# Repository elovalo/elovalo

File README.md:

<!-- -*- mode: markdown; coding: utf-8 -*- -->

# Elovalo LED Cube Pedestal

You should check out [elovalo.koodilehto.fi](http://elovalo.koodilehto.fi/) for more casual documentation. If you are interested in building the project and developing effects, read on.

## Dependencies

You should have at least gcc, avr-gcc, scons, gperf and preferably
jansson and Blender installed in order to use the simulator. If you
have Ubuntu 12.04 LTS or 12.10, we have instructions for you.

### Ubuntu 14.10

Something went wrong with GCC leading to this project not to compile. We are going to fix this after release of Ubuntu 15.04. If you happen te fix it, please send a patch!

### Ubuntu 12.10

To build on Ubuntu 12.10, install the following packages:

    sudo apt-get install gcc-avr avr-libc gcc scons libjansson-dev gperf avrdude

If you want to generate animations, install the following packages as well:

    sudo apt-get install blender libav-tools

### Ubuntu 12.04

With Ubuntu 12.04 LTS you need to install some packages from Quantal (12.10)
repositories. Here's how to do it:

Add the following lines to <tt>/etc/apt/preferences.d/10-quantal</tt>

    Package: *
    Pin: release a=quantal
    Pin-Priority: 100

And add the following line to <tt>/etc/apt/sources.list</tt>

    deb http://archive.ubuntu.com/ubuntu quantal main restricted universe multiverse

Now you can install all the required packages:

    sudo apt-get install gcc-avr/quantal avr-libc/quantal gcc scons libjansson-dev gperf avrdude

If you want to generate animations, install the following packages as well:

    sudo apt-get install blender libav-tools

The alternative to using quantal-pinning is to fetch the packages from
launchpad. This has only been verified on Kubuntu. You can also skip
the above steps and download the packages straight from the quantal
launchpad:
	
	https://launchpad.net/ubuntu/quantal/amd64/avr-libc/1:1.8.0-2
	https://launchpad.net/ubuntu/quantal/amd64/gcc-avr

If you have a 32bit system (tell 2002 we said *hi*), replace the amd64
from the URL to i386.

### OS X with SCons

Make sure you have at least gcc, avr-gcc and scons
installed. Preferably you should have jansson and Blender (2.6x) as
well if you wish to use the simulator.

In order to render with Blender, you'll need to define an alias
for. Just having it in your path isn't quite enough for some
reason. Add something like this to your .bashrc or .bash\_profile:

    alias blender="path to blender/blender.app/Contents/MacOS/blender"

### Eclipse 

You may use Eclipse for editing but you need SCons because of the complexity of this build (we are using code generation and multiple targets). It may be possible to use SCons in Eclipse if you feel adventurous:
http://stackoverflow.com/questions/1052759/eclipse-cdt-scons

## Building with SCons

The recommended way to build this project is SCons and we have
SCons build file for you. Just run:

    scons

Then the AVR output gets into `build/elo` and `build/zcl` and exporter
stuff to `build/exporter`. To run the exporter:

    build/exporter/exporter

If you want just to play with effets and you don't have an AVR compiler,
you may skip AVR build by running:

    scons --no-avr

## Programming AVR with SCons

If you are running Ubuntu 12.04 or newer and want to be able to flash without
root privileges, add the following udev rule to `/etc/udev/rules.d/10-usbasp`:

    SUBSYSTEM=="usb", ATTR{idVendor}=="16c0", ATTR{idProduct}=="05dc", MODE="0660", GROUP="adm"

Then just reboot your computer (or do some udev magic if you are Linux master).

To program Elocmd variant (the ordinary one), run:

    scons --program-elo
	
To program the variant with Zigbee support, run:

    scons --program-zcl

## Size Optimization

There is enough EEPROM but the SRAM usage is quite high because of
front and back buffers uses 0x300 bytes each. This leaves very scarce
resources for effect development. To see contents of SRAM, run:

    avr-objdump -t -j .data -j .bss build/zcl/release/firmware.elf

Bytes used in SRAM is printed every time scons is run. SRAM size in
ATmega328p is 2048 bytes. If SRAM gets too full, there is not enough
space for run-time stack. If so, you are in need of optimization.

If there are large arrays of constant data you should place the data
in program memory. See code in effects.c and main.c about effects[]
access. Also, read the following:

- http://nongnu.org/avr-libc/user-manual/pgmspace.html

- http://www.atmel.com/Images/doc8453.pdf

## Other

If you study the project further, you'll find more READMEs and more information related to specific parts. Have fun developing effects and whatnot!

## Credits

* [Joni Katajamäki](https://github.com/katis) - Embedded programming, hardware design 
* [Jukka Kinnunen](https://github.com/resutoor) - Hardware design and debugging
* [Joel Lehtonen](https://github.com/Zouppen/) - Embedded programming, effect engine programming
* [Lasse Saari](https://github.com/lassesaari) - Management, pedestal fabrication
* [Marko Silokunnas](https://github.com/marant) - Soldering
* [Mio Taalas](https://github.com/mtaalas/) - LED driver interface design, PCB design,
  embedded programming
* [Ilkka Turunen](https://github.com/ile2/) - Management, soldering, pedestal
  tests and aesthetic design
* [Juho Vepsäläinen](https://github.com/bebraw/) - 3D simulator, effect programming, pedestal
  design

## License

We use GPLv3 for software. Create Commons Attribution-ShareAlike is used for hardware and accompanying documentation. See LICENSE files for more details.

If you create a derivative, please let us know. It would be interesting to hear what you are doing.

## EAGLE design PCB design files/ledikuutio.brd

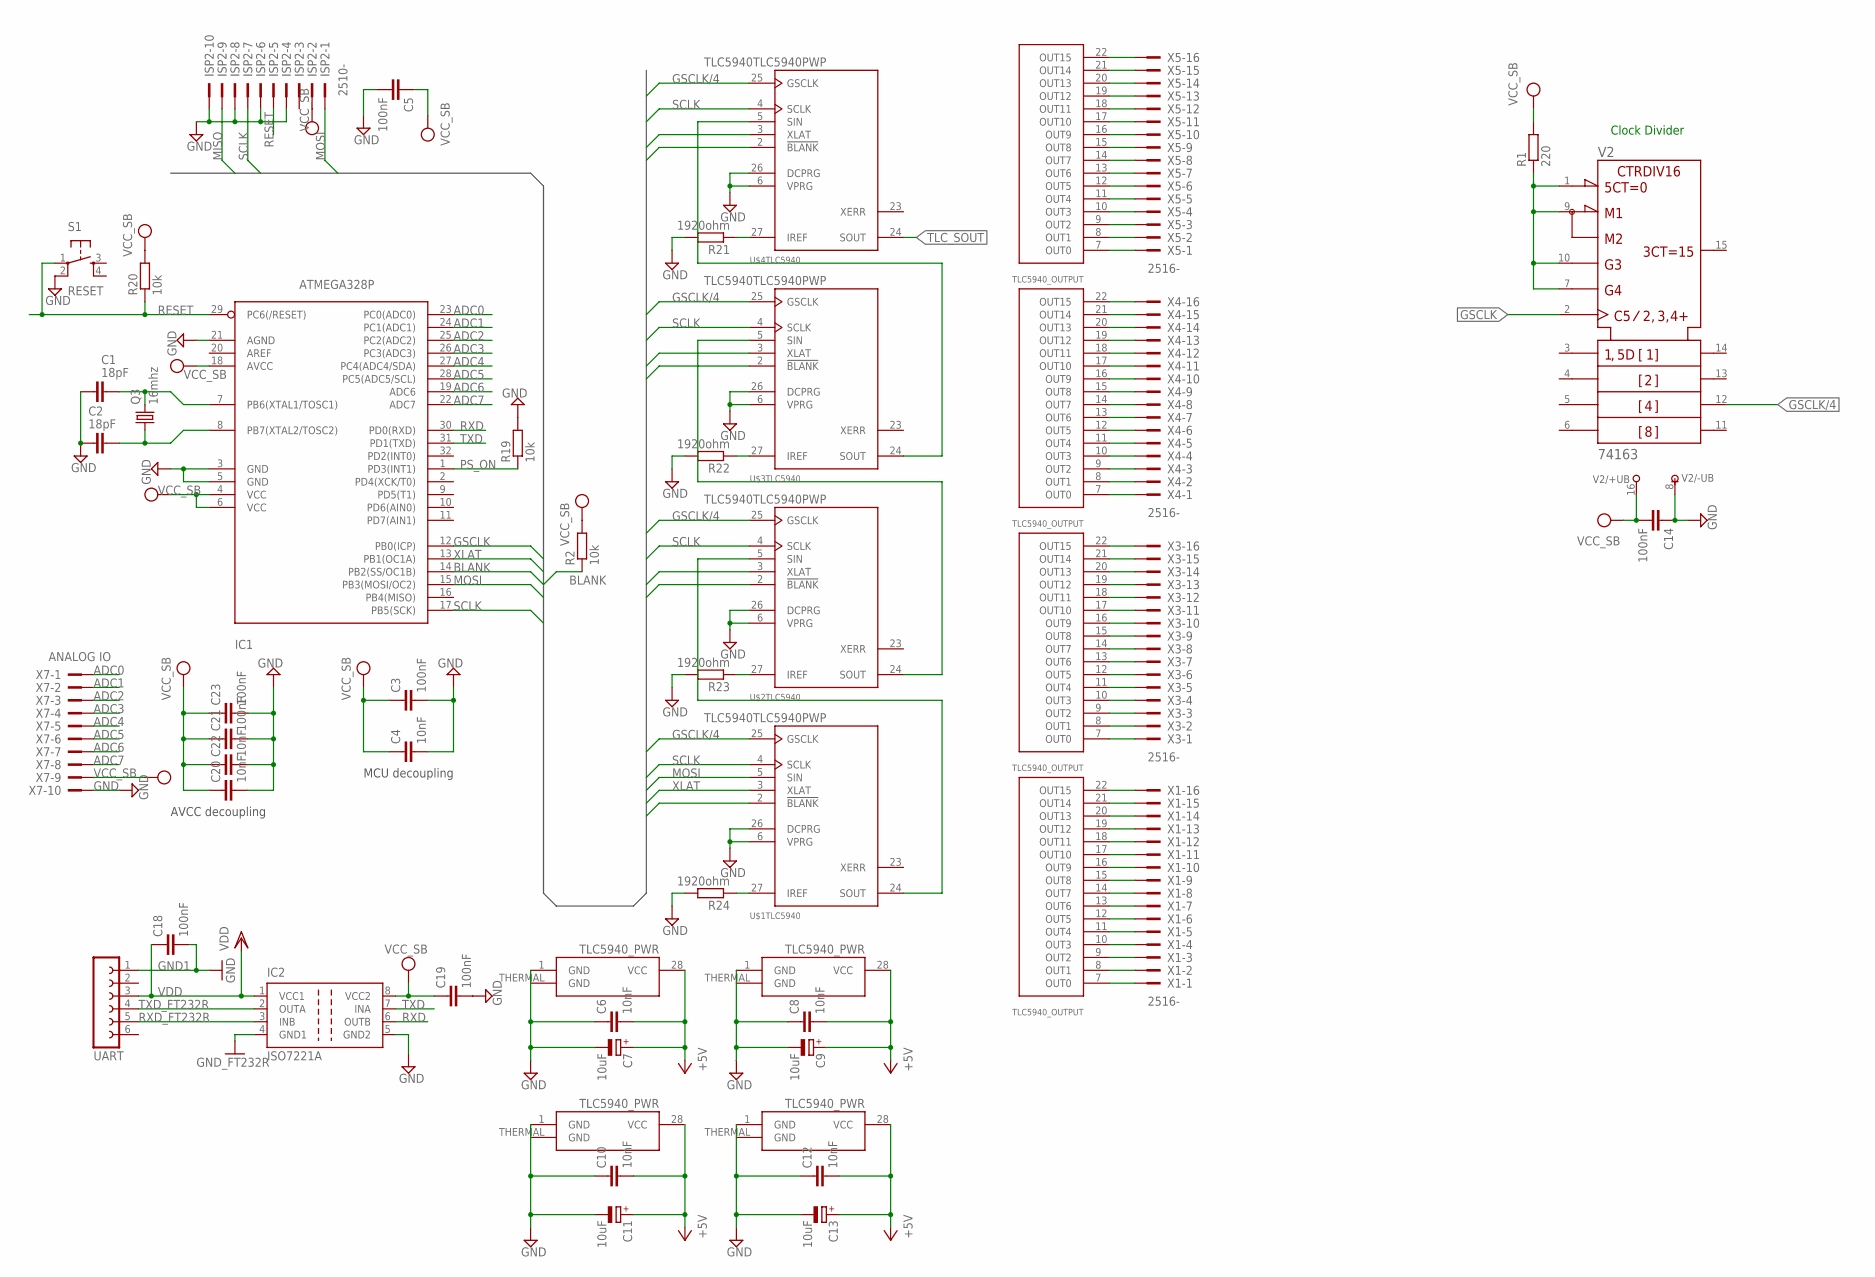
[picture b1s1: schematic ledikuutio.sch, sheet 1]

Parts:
C1, C2: 18pF; C0805
C3, C5, C14, C21, C23: 100nF; C0805
C4, C6, C8, C10, C12, C20, C22: 10nF; C0805
C7, C9, C11, C13: 10uF; E2,5-6
C18, C19: 100nF; C0603
IC1: ATMEGA328P; TQFP32-08
IC2: ISO7221A; SO-08
ISP2: 2510-; PAK100/2500-10
Q3: 16mhz; CRYSTAL-SMD-5X3
R1: 220; M0805
R2, R19, R20: 10k; M0805
R21, R22, R23, R24: 1920ohm; M0805
S1: RESET; TACTILE_SWITCH_SMD
U$1, U$2, U$3, U$4: TLC5940TLC5940PWP; PWP28
UART: FE06-1; FE06
V2: 74163; SO16
X1, X3, X4, X5: 2516-; PAK100/2500-16
X7: ANALOG IO; PAK100/2500-10

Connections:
+5V: C6.2, C7.+, C8.2, C9.+, C10.2, C11.+, C12.2, C13.+, U$1.28 (VCC), U$2.28 (VCC), U$3.28 (VCC), U$4.28 (VCC); also elsewhere on the board
ADC0: IC1.23 (PC0(ADC0)), X7.1
ADC1: IC1.24 (PC1(ADC1)), X7.2
ADC2: IC1.25 (PC2(ADC2)), X7.3
ADC3: IC1.26 (PC3(ADC3)), X7.4
ADC4: IC1.27 (PC4(ADC4/SDA)), X7.5
ADC5: IC1.28 (PC5(ADC5/SCL)), X7.6
ADC6: IC1.19 (ADC6), X7.7
ADC7: IC1.22 (ADC7), X7.8
BLANK: IC1.14 (PB2(SS/OC1B)), R2.1, U$1.2 (!BLANK), U$2.2 (!BLANK), U$3.2 (!BLANK), U$4.2 (!BLANK)
GND: C1.1, C2.2, C3.2, C4.2, C5.2, C6.1, C7.-, C8.1, C9.-, C10.1, C11.-, C12.1, C13.-, C14.1, C19.2, C20.2, C21.2, C22.2, C23.2, IC1.3 (GND), IC1.5 (GND), IC1.21 (AGND), IC2.5 (GND2), ISP2.4, ISP2.6, ISP2.8, ISP2.10, R19.2, R21.2, R22.2, R23.2, R24.2, S1.2, U$1.1 (GND), U$1.6 (VPRG), U$1.26 (DCPRG), U$1.THERMAL (GND), U$2.1 (GND), U$2.6 (VPRG), U$2.26 (DCPRG), U$2.THERMAL (GND), U$3.1 (GND), U$3.6 (VPRG), U$3.26 (DCPRG), U$3.THERMAL (GND), U$4.1 (GND), U$4.6 (VPRG), U$4.26 (DCPRG), U$4.THERMAL (GND), V2.8 (-UB), X7.10; also elsewhere on the board
GND1: C18.2, IC2.4 (GND1), UART.1
GSCLK: IC1.12 (PB0(ICP)), V2.2 (CLK)
GSCLK/4: U$1.25 (GSCLK), U$2.25 (GSCLK), U$3.25 (GSCLK), U$4.25 (GSCLK), V2.12 (QC)
MISO: IC1.16 (PB4(MISO)), ISP2.9
MOSI: IC1.15 (PB3(MOSI/OC2)), ISP2.1, U$1.5 (SIN)
unnamed: U$1.24 (SOUT), U$2.5 (SIN)
unnamed: C1.2, IC1.7 (PB6(XTAL1/TOSC1)), Q3.3 (2)
unnamed: C2.1, IC1.8 (PB7(XTAL2/TOSC2)), Q3.1
unnamed: U$2.24 (SOUT), U$3.5 (SIN)
unnamed: R21.1, U$4.27 (IREF)
unnamed: R23.1, U$2.27 (IREF)
unnamed: U$1.7 (OUT0), X1.1
unnamed: U$1.8 (OUT1), X1.2
unnamed: U$1.9 (OUT2), X1.3
unnamed: U$1.10 (OUT3), X1.4
unnamed: U$1.11 (OUT4), X1.5
unnamed: U$1.12 (OUT5), X1.6
unnamed: U$1.13 (OUT6), X1.7
unnamed: U$1.14 (OUT7), X1.8
unnamed: U$1.15 (OUT8), X1.9
unnamed: U$1.16 (OUT9), X1.10
unnamed: U$1.17 (OUT10), X1.11
unnamed: U$1.18 (OUT11), X1.12
unnamed: U$1.19 (OUT12), X1.13
unnamed: U$1.20 (OUT13), X1.14
unnamed: U$1.21 (OUT14), X1.15
unnamed: U$1.22 (OUT15), X1.16
unnamed: R24.1, U$1.27 (IREF)
unnamed: U$2.7 (OUT0), X3.1
unnamed: U$2.8 (OUT1), X3.2
unnamed: U$2.9 (OUT2), X3.3
unnamed: U$2.10 (OUT3), X3.4
unnamed: U$2.11 (OUT4), X3.5
unnamed: U$2.12 (OUT5), X3.6
unnamed: U$2.13 (OUT6), X3.7
unnamed: U$2.14 (OUT7), X3.8
unnamed: U$2.15 (OUT8), X3.9
unnamed: U$2.16 (OUT9), X3.10
unnamed: U$2.17 (OUT10), X3.11
unnamed: U$2.18 (OUT11), X3.12
unnamed: U$2.19 (OUT12), X3.13
unnamed: U$2.20 (OUT13), X3.14
unnamed: U$2.21 (OUT14), X3.15
unnamed: U$2.22 (OUT15), X3.16
unnamed: U$3.7 (OUT0), X4.1
unnamed: U$3.8 (OUT1), X4.2
unnamed: U$3.9 (OUT2), X4.3
unnamed: U$3.10 (OUT3), X4.4
unnamed: U$3.11 (OUT4), X4.5
unnamed: U$3.12 (OUT5), X4.6
unnamed: U$3.13 (OUT6), X4.7
unnamed: U$3.14 (OUT7), X4.8
unnamed: U$3.15 (OUT8), X4.9
unnamed: U$3.16 (OUT9), X4.10
unnamed: U$3.17 (OUT10), X4.11
unnamed: U$3.18 (OUT11), X4.12
unnamed: U$3.19 (OUT12), X4.13
unnamed: U$3.20 (OUT13), X4.14
unnamed: U$3.21 (OUT14), X4.15
unnamed: U$3.22 (OUT15), X4.16
unnamed: U$4.7 (OUT0), X5.1
unnamed: U$4.8 (OUT1), X5.2
unnamed: U$4.9 (OUT2), X5.3
unnamed: U$4.10 (OUT3), X5.4
unnamed: U$4.11 (OUT4), X5.5
unnamed: U$4.12 (OUT5), X5.6
unnamed: U$4.13 (OUT6), X5.7
unnamed: U$4.14 (OUT7), X5.8
unnamed: U$4.15 (OUT8), X5.9
unnamed: U$4.16 (OUT9), X5.10
unnamed: U$4.17 (OUT10), X5.11
unnamed: U$4.18 (OUT11), X5.12
unnamed: U$4.19 (OUT12), X5.13
unnamed: U$4.20 (OUT13), X5.14
unnamed: U$4.21 (OUT14), X5.15
unnamed: U$4.22 (OUT15), X5.16
unnamed: U$3.24 (SOUT), U$4.5 (SIN)
unnamed: R1.1, V2.1 (!CLR), V2.7 (ENP), V2.9 (!LOAD), V2.10 (ENT)
unnamed: R22.1, U$3.27 (IREF)
PS_ON: IC1.1 (PD3(INT1)), R19.1; also elsewhere on the board
RESET: IC1.29 (PC6(/RESET)), ISP2.5, R20.1, S1.1
RXD: IC1.30 (PD0(RXD)), IC2.6 (OUTB)
RXD_FT232R: IC2.3 (INB), UART.5
SCLK: IC1.17 (PB5(SCK)), ISP2.7, U$1.4 (SCLK), U$2.4 (SCLK), U$3.4 (SCLK), U$4.4 (SCLK); also elsewhere on the board
TLC_SOUT: U$4.24 (SOUT); also elsewhere on the board
TXD: IC1.31 (PD1(TXD)), IC2.7 (INA)
TXD_FT232R: IC2.2 (OUTA), UART.4
VCC: C3.1, C4.1, C5.1, C14.2, C19.1, C20.1, C21.1, C22.1, C23.1, IC1.4 (VCC), IC1.6 (VCC), IC1.18 (AVCC), IC2.8 (VCC2), ISP2.2, R1.2, R2.2, R20.2, V2.16 (+UB), X7.9; also elsewhere on the board
VDD: C18.1, IC2.1 (VCC1), UART.3
XLAT: IC1.13 (PB1(OC1A)), U$1.3 (XLAT), U$2.3 (XLAT), U$3.3 (XLAT), U$4.3 (XLAT); also elsewhere on the board

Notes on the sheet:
MCU decoupling
Clock Divider
AVCC decoupling

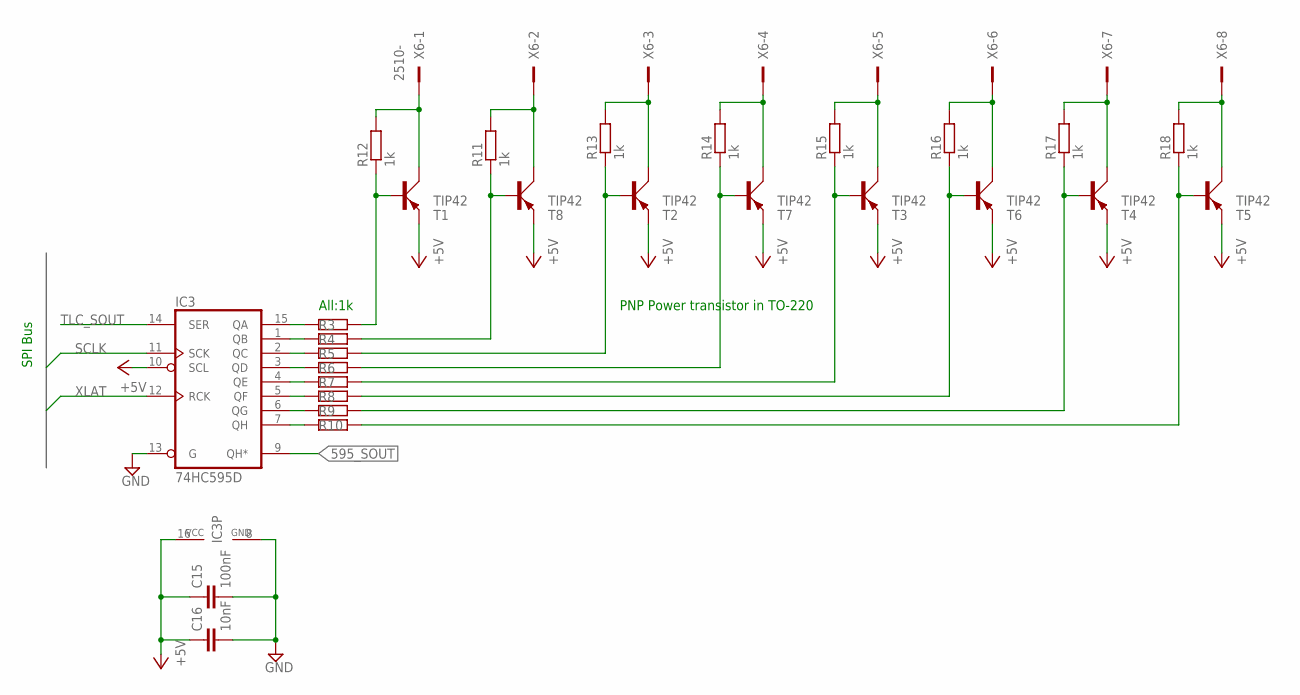
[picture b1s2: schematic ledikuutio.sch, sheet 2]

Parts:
C15: 100nF; C0805
C16: 10nF; C0805
IC3: 74HC595D; SO16
R3, R4, R5, R6, R7, R8, R9, R10, R11, R12, R13, R14, R15, R16, R17, R18: 1k; M0805
T1, T2, T3, T4, T5, T6, T7, T8: TIP42; TO220AV
X6: 2510-; PAK100/2500-10

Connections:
595_SOUT: IC3.9 (QH*)
+5V: C15.1, C16.1, IC3.10 (SCL), IC3.16 (VCC), T1.E, T2.E, T3.E, T4.E, T5.E, T6.E, T7.E, T8.E; also elsewhere on the board
GND: C15.2, C16.2, IC3.8 (GND), IC3.13 (G); also elsewhere on the board
unnamed: R11.2, T8.C, X6.2
unnamed: R14.2, T7.C, X6.4
unnamed: R16.2, T6.C, X6.6
unnamed: R18.2, T5.C, X6.8
unnamed: R12.2, T1.C, X6.1
unnamed: R13.2, T2.C, X6.3
unnamed: R15.2, T3.C, X6.5
unnamed: R17.2, T4.C, X6.7
unnamed: IC3.15 (QA), R3.1
unnamed: IC3.1 (QB), R4.1
unnamed: IC3.2 (QC), R5.1
unnamed: IC3.3 (QD), R6.1
unnamed: IC3.4 (QE), R7.1
unnamed: IC3.5 (QF), R8.1
unnamed: IC3.6 (QG), R9.1
unnamed: IC3.7 (QH), R10.1
unnamed: R5.2, R13.1, T2.B
unnamed: R3.2, R12.1, T1.B
unnamed: R4.2, R11.1, T8.B
unnamed: R6.2, R14.1, T7.B
unnamed: R7.2, R15.1, T3.B
unnamed: R8.2, R16.1, T6.B
unnamed: R9.2, R17.1, T4.B
unnamed: R10.2, R18.1, T5.B
SCLK: IC3.11 (SCK); also elsewhere on the board
TLC_SOUT: IC3.14 (SER); also elsewhere on the board
XLAT: IC3.12 (RCK); also elsewhere on the board

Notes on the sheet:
All:1k
SPI Bus
PNP Power transistor in TO-220

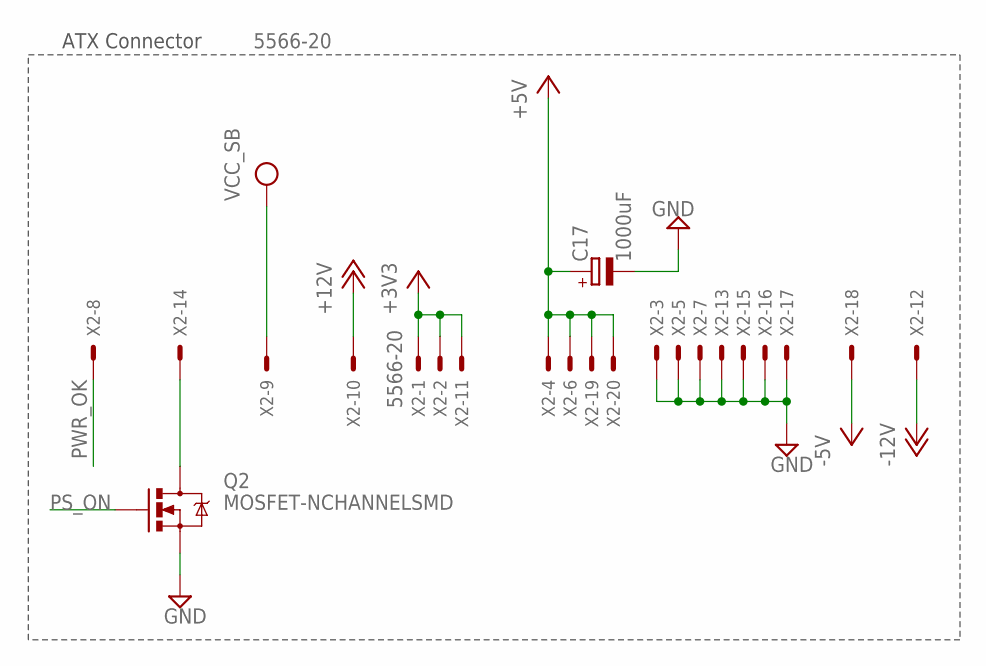
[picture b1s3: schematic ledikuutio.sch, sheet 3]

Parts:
C17: 1000uF; E3,5-10
Q2: MOSFET-NCHANNELSMD; SOT23-3
X2: 5566-20

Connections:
+3V3: X2.1, X2.2, X2.11
+5V: C17.+, X2.4, X2.6, X2.19, X2.20; also elsewhere on the board
+12V: X2.10
-5V: X2.18
-12V: X2.12
GND: C17.-, Q2.2 (S), X2.3, X2.5, X2.7, X2.13, X2.15, X2.16, X2.17; also elsewhere on the board
unnamed: Q2.3 (D), X2.14
PS_ON: Q2.1 (G); also elsewhere on the board
PWR_OK: X2.8
VCC: X2.9; also elsewhere on the board

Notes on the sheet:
ATX Connector

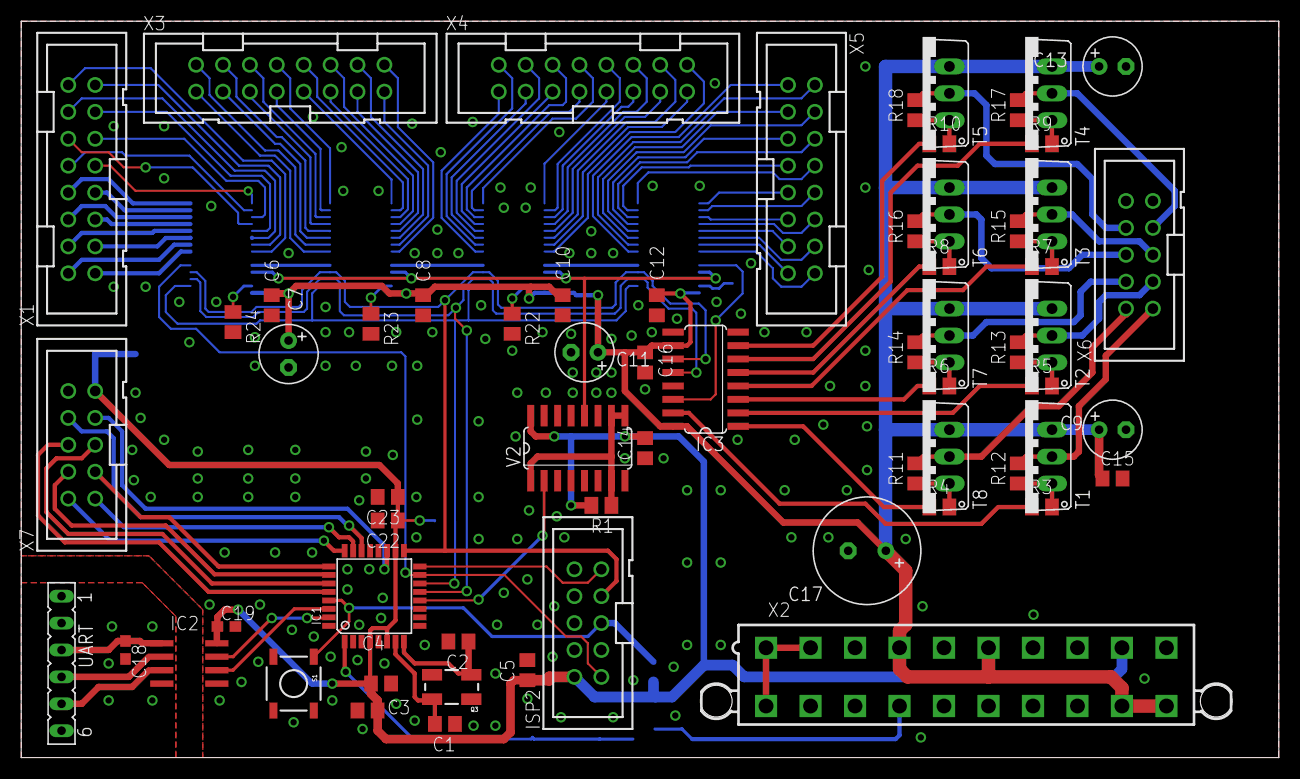
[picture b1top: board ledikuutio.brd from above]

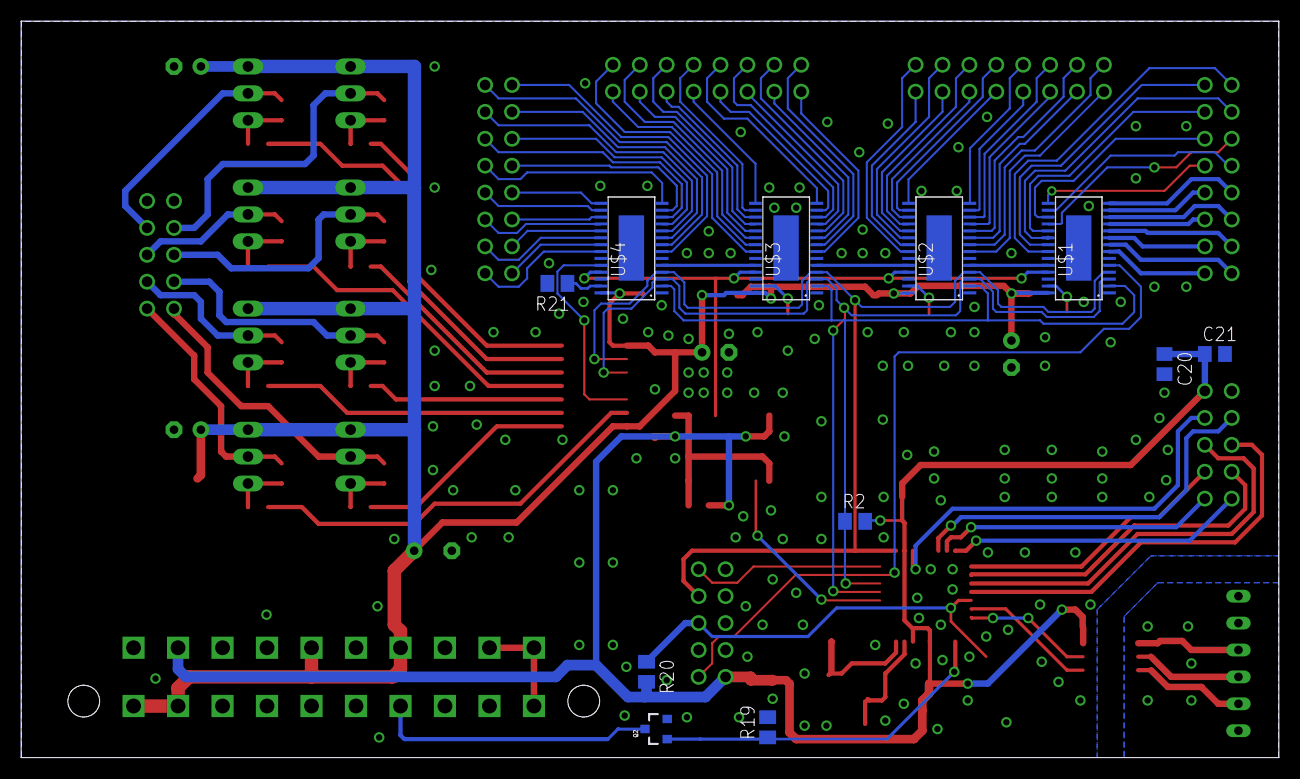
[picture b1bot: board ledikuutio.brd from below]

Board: 2 copper layers, 118.7 x 69.5 mm, 75 parts (11 on the bottom side), 127 nets.

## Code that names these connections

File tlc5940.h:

/*
 * tlc5940.h
 *
 *  Created on: 12.6.2012
 *      Author: Icchan
 */

#ifndef TLC5940_H_
#define TLC5940_H_

#define TLC5940 1 //Number of devices
#define GS_DATA_LENGHT (TLC5940*24)-1 //One layers data length
#define DC_DATA_LENGTH (TLC5940*12)-1 //Dot correction data lenght for one layer
#define USE_EEPROM_DC_DATA 1 //Use preprogrammed EEPROMdata in dot correction

//Define IO

/**TLC5940 pins*/
#define DCPRG 	D,PD2 /*Changes if the DC data is written to the EEPROM (low) or to the register (high)*/
#define VPRG 	D,PD3 //when high, TLC5940 is in DC mode, while low, in GS mode
#define XLAT 	B,PB1 //Data latch from shift register to the device registers
#define BLANK 	B,PB2 //BLANK every 4096 GScycles. Digital pin 10 ARDUINO

//SPI pins
#define MOSI 	B,PB3
#define MISO 	B,PB4
#define CLK 	B,PB5
#define SCLK 	CLK //For the TLC5940 abstraction... see flowchart.

//Global variables...

extern uint8_t FirstCycle ;
extern uint8_t GSdataCounter;
extern uint8_t DCdataCounter;
extern volatile uint8_t c;
extern uint8_t isAfterFlip;

void initTLC5940();

void DCInputCycle();

void InitGScycle();

#endif /* TLC5940_H_ */

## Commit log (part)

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2012-09-20 Register allocation is working again. Closes #61.
    LTO partitioning makes register allocations invisible to other
    partitions. When given -flto-partition=none it turns off partitioning
    and the linker sees all register allocations in all parts of the code
    base.
    It broke because our codebase has expanded and it didn't fit inside
    one LTO partition. Dear GCC people, please fix this.
2012-09-20 Pass sensor data to exporter properly
    It needs to be before custom data.
2012-09-20 Add dummy sensor data
    This generates just a bunch of ones.
2012-09-20 Add jansson library support and some pkgconfig stuff
2012-09-20 Add partial support for the new serial port protocol
    Reading and commanding effects and actions works
2012-09-21 Add environment to make the build work ok on os x
2012-09-21 Hook up sensor data with exporter
2012-09-21 Fix init_current_effect() to do buffer preparation. #33
2012-09-21 effects: Add stairs_y which helps debugging wiring
2012-09-21 Add "AVR-friendly" assert.h
2012-09-21 Generate more sensible playlist code
    Now it uses PROGMEM properly.
2012-09-21 Include stdlib at generated playlist
2012-09-21 Generate proper hex
2012-09-21 Define initial playlist for park
2012-09-21 Add missing include and tweak default text
    Still not rendering in simulator, though. Need to fix this.
2012-09-21 Add irc nicks to credits
2012-09-21 Clear heart at init
2012-09-21 effects: Multiply rain random seed with 3 to make it prettier
2012-09-21 Start the firmware in kiosk mode (autonomous playlist iteration)
2012-09-21 Remove effect challenge bit since it is not relevant anymore
2012-09-23 Implement finite worm
    Closes #63.
2012-09-23 Add a chance for mutation
2012-09-23 Document sensors usage
    Closes #68.
2012-09-23 Tidy up README structure
2012-09-23 Fix exporter running speed, custom_data passing, and tick incremention
2012-09-23 Optimize by rendering only two characters simultaneously. Closes #70
2012-09-24 Tidy up text rendering API
2012-09-24 AVR goes to SLEEP when cube is off. Some timers are disabled. #15
2012-09-24 Add clock-based random number generator and initialize it in every init.
2012-09-24 Parametrizing finite worm length
2012-09-24 Fix typo in time.h
2012-09-24 effects: Faster sine, because of the heat of urban city of Jyväskylä
2012-09-25 Stop execution of simulator if build fails
2012-09-25 Catch build and export fail in a nicer way
2012-09-25 Tidy up text API
    Defined a couple of generic text rendering callbacks and made various effects
    use those.
2012-09-25 Weber–Fechner with s0 variable
    s0 allows us to define a minimum value of intensity which human
    doesn't percieve when looking a LED cube.
    Not sure about the mathematical validity but seems to work well with
    my values.
2012-09-26 Add new variant 'simulation' which is AVR build with special features
    Simulation target doesn't use SLEEP instruction which makes simulavr
    to slow down too much. Also, it adds special case to timer interrupt
    which runs BREAK instruction and halts execution 25 times a second to
    allow front buffer extraction by avr-gdb.
    Not integrated to the simulator yet.
2012-09-27 Set Weber-Fechner threshold (s0) to 10
2012-09-27 Use Weber–Fechner to draw heart intensity. Not perfect, though.
2012-09-27 Add distance interactivity to wave
2012-09-28 Cast XML playlist length to int
    Thanks to @resutoor for pointing this one out!
2012-09-28 Smaller duration to winter is coming text
2012-09-30 simuation: Some work with memory to array mapping
2012-09-30 simulation: Array parsing and voxel extraction works
2012-10-06 Added C2IS ElovaloEP ZCL-type specifications initial version
2012-10-06 Added some new attributes to ElovaloEP
2012-10-06 Add link to facebook
2012-10-07 Fix typo in Protomo booth playlist file
2012-10-07 Updating preliminary specs
2012-10-08 Update README to reflect frustrations with a fresh ubuntu install.
2012-10-10 Add serial functions for reading hex encoded messages
2012-10-10 Add functions for encoding and decoding hex data to/from serial port
2012-10-10 Move changing playlists and effects to their own functions
2012-10-10 Remove unused includes from serial_elo
2012-10-10 PROGMEM compatible renderer. No UTF-8 parser yet, but should work with ASCII.
2012-10-11 Use pointer memory type detection in mb_pgm_get
    This allows to access progmem without knowing if pointer is in
    PROGMEM. Changed all effects to leave out pgmspace flag.
2012-10-11 Fixed removed includes
2012-10-11 build: Add ZCL and ELO variants to build and programming system
2012-10-13 Implement preprocessor for converting UTF-8 strings
    It is implemented a bit dirty way by running scons inside scons. It's
    only way to force the source to be compiled before others.
2012-10-14 Added how to use c2cs message debugger
2012-10-14 Add PROGMEM copying function to ease handling of structs
2012-10-14 Make the effects to use the new text rendering API
2012-10-14 Use dynamic allocation in glyph converter and use line buffering
    Without line buffering it was using block buffering which broke code
    generation part which transcoded UTF-8 to glyph_buf.
2012-10-14 Fix issue when array grew above 256 glyphs
2012-10-14 Add untested ZCL skeleton
    reads from serial port and tries to handle from frame -> ZCL command
    frame
2012-10-14 Add line numbers to effects.c output
    Closes #76.
2012-10-14 Fixed rendering errors. Cyrillic works.
2012-10-14 Add return to ZCL serial communication if ATI received
2012-10-14 Add xpm2Elogperf converter to helper script portfolio
2012-10-15 There should be no global schedule and cube should start immediately
    In future there should be some environment specific crontabs. While we
    are not there yet, just remove them. Also, fixed an issue where the
    cube was unable to start after power-up.
2012-10-17 Convert gperf binaries to hex
    This is needed for GCC 4.3<.
2012-10-17 Move generated effects and playlists to generated/ directory
    Closes #81.
2012-10-17 Move commonly shared source files to common/
    Closes #80.
2012-10-20 Update building instructions
2012-10-20 Fix include
2012-10-20 Check z axis, just ignore it if it is out of bounds, don't assert
2012-10-20 Add all-off and blinker effect. Blinker has constant blink rate
2012-10-21 Mark alias=blender as code
2012-10-24 Update length of Pöö
2012-10-25 Fix missing track from ISP header.
2012-10-28 Removed old ZCL files
2012-10-28 Add initial ATI support
2012-10-28 Playlist conf file name fixed
2012-10-29 Remove redundant stylesheets
2012-10-29 Show map only for desktop
    Perhaps that should be shown for tablet as well. That might require different
    kind of layout, though.
2012-10-29 Make footer look better
2012-10-29 Render news so that they fill area properly
    Previously there were some overlap issues. In certain case there was too much
    empty space.
2012-10-29 Add news header
2012-10-29 Make map scale properly
2012-10-29 Remove view on larger map
    Not going to need that.
2012-10-29 Fixed bit shifts and some erronous write code
2012-10-29 Remove _site
2012-10-29 Remove redundant directory
2012-10-29 Send ACK instead of NAK if message has wrong MAC
2012-10-29 Get rid of unused variable warning with SIMU target
2012-10-29 pgmspace.h is moved to common, change include path accordingly
2012-10-31 Make zcl reading functions use a function pointer for reading bytes
2012-10-31 Revert "Fixed iterating over the length of zcl messages"
    This reverts commit d1f10761727aa2a96821a5103abab10283a00ee1.
2012-11-01 Hook up timeline initially
    Still something weird going on. Not loading. Might configuration or service
    related. We actually might be better off by using some another timeline widget
    that does not depend on external service. iframes are nasty.
2012-11-01 Add stubs for timeline JSON load
2012-11-01 Hook up FB data with timeline
2012-11-01 Decode FB post titles properly
2012-11-02 Add links to wire messages
2012-11-02 Defining reader_t helpers as macros instead of pointers to save memory
2012-11-02 Rename hex_val_t struct values
2012-11-02 Refactored reading of ZCL message header. Using bools where possible.
2012-11-03 Refactor zcl reader function defines to all caps
2012-11-03 Use booleans in process_payload() and proces_cmd_frame return types
2012-11-03 Add serial buffer length, too. Is 768 bytes in 8x8x8 configuration
2012-11-03 ZCL struct is fitted inside gs_buf_back with clever type caster macros
    Refactoring is still in progress but this should be able to parse ZCL
    command frame. Read and write functions are not corrected.
2012-11-04 Remove references to read_crc
2012-11-04 Make youtube videos render better at timeline
2012-11-04 Move AVR target specific parts to serial_target
2012-11-06 serial: Reorganized send functions to the beginning of serial.c
2012-11-06 Fix hexadecimal encoding in ZCL
2012-11-06 Add purchasing info to licensing and purchasing
    Kind of pointless to have that section otherwise. Also removed the tidbit from
    the bottom since it became redundant now.
2012-11-07 Add time read and write support for ZCL protocol
2012-11-07 Serial library visibility changes. Prepares big serial reform.
2012-11-07 serial: tx_state must be not static but public
2012-11-07 serial_zcl: Polish the API and document its functions
2012-11-07 serial_zcl: Making more helper functions for public use
2012-11-07 Answer of ATI is triggeref from 'I' instead of carriage return / newline
    This makes it more robust to DOS linefeeds by answering only once. The
    old linefeed trick was vulnerable to that. Also, 'I' is not used
    anywhere in packet format so it should be safe.
2012-11-08 Remove redundant JS
2012-11-14 Internal error handling (buffer overrun) added to ZCL varian
2012-11-14 Fix mac checking and writing
2012-11-14 Move IEEE read to Elovalo cluster in ZCL
2012-11-14 Fix ZigBee time offset in stime()
2012-11-14 Fix warning in serial_target
2012-11-15 Link to brochure
2012-11-15 Refactor write_# functions to not need writers
    Also remove accept() function as unnecessary
2012-11-15 Rename message reads, using msg_get_# scheme
2012-11-15 Handle default response command
2012-11-15 Respond to hardware and software versions
2012-11-22 Rename writeI_# functions to send_#
2012-11-22 Add error responses to incorrect cluster and command type
2012-11-22 Support active effect attribute
2012-11-22 Add sending length to the effect names
2012-11-22 Store timezone to EEPROM. On exporter, use hard-wired UTC timezone.
2012-11-22 Use playlist item pointers instead of values with ZCL listing
2012-11-22 Calculate effect JSON length at compile-time
2012-11-22 Fix cluster and attribute IDs of IEEE address to match implementation on server
2012-11-27 Use simpler EEPROM accessing functions time zone
2012-12-04 Add startup mode picker for AVR_ZCL. Fix bug in main.h
2012-12-04 Fix issue when effect was changed while in MODE_EFFECT
2012-12-04 Remove extra check from effect and playlist initialization
2012-12-04 Support MODE_SLEEP setting via ZCL message
2012-12-09 Make the exporter take simulator data in count properly
    Previously it failed to use the data in the right way. It should it now.
2012-12-11 Refactored UTF-8 decoder
2012-12-11 Implement text writing support to EEPROM
2012-12-11 Custom text is now stored in EEPROM and displayed at effect_text. Closes #91.
2012-12-11 Playlist position support. Closes #93
2012-12-11 MAC address should be correct in ATI response
2013-01-09 Unify 'anim' and 'render' to a single command, 'render'
    Instead of having to swap between the commands, now you can just use the
    following syntax:
    ./render <effect> <target> <frame>?
    As you can see that 'frame' bit is optional. If skipped, it will render the
    whole animation. Optional arguments defined earlier apply still.
2013-01-09 Wrapping scroll_text, closes #103
2013-01-09 Add modified text mark to main function
2013-01-13 Output playlist names in JSON. Closes #89
2013-01-13 Implement playlist string sending (closes #94)
2013-01-13 Add support for receiving time over Zigbee reporting
2013-01-13 Ugly trick to force variable-length structure to allocate itself.
2013-01-13 Rolling clock (closes #92)
2013-01-20 Restart effect after tick counter reaches maximum. #113
2013-01-26 Support exporting to binary format using -b / --binary flag
    Closes #115.
2013-01-26 Fix syntax errors and incorrect baudrate in Elocmd
2013-01-26 Minor fix for reading the beginning response of the file send in elocmd
2013-01-26 Elocmd can now send effect data from files to the cube
2013-01-26 elocmd: Add support for uploading a playlist of effects
2013-01-26 exporter: Convert characters to glyphs before passing to custom_data
    This closes #117.
2014-09-19 Update CNAME
    Domain expired, moving it under Koodilehto.
2014-09-19 Show news entries only till 2013
2015-03-13 Delete TODO.txt
    All this is done but the file was left behind.
2015-03-13 Update README.md
    Fix a link label
2015-03-13 Update README.md
    Some rephrasing
